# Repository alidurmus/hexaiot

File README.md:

# hexaiot
Open source hardware iot project

What is IOT?
The internet of things, or IoT, is a system of interrelated computing devices, mechanical and digital machines, objects, animals or people that are provided with unique identifiers (UIDs) and the ability to transfer data over a network without requiring human-to-human or human-to-computer interaction

Why is IOT?
Increasingly, organizations in a variety of industries are using IoT to operate more efficiently, better understand customers to deliver enhanced customer service, improve decision-making and increase the value of the business.

History Of IOT
Kevin Ashton, co-founder of the Auto-ID Center at MIT, first mentioned the internet of things in a presentation he made to Procter & Gamble (P&G) in 1999. Wanting to bring radio frequency ID (RFID) to the attention of P&G’s senior management, Ashton called his presentation “Internet of Things” to incorporate the cool new trend of 1999: the internet. MIT professor Neil Gershenfeld’s book, When Things Start to Think, also appearing in 1999, didn’t use the exact term but provided a clear vision of where IoT was headed.

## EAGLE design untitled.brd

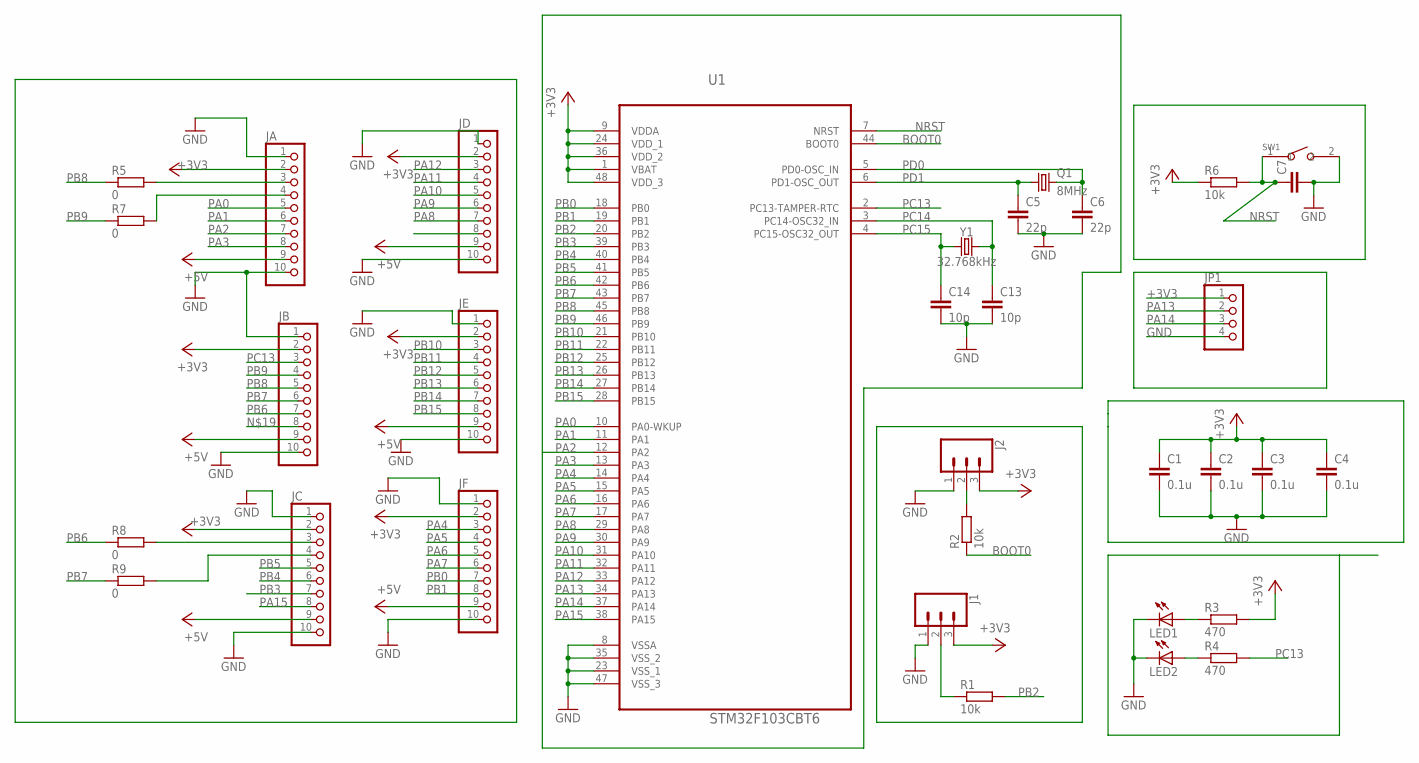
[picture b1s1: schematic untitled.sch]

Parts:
C1, C2, C3, C4: 0.1u; C0805K
C5, C6: 22p; C0805K
C7: C-EUC0805K; C0805K
C13, C14: 10p; C1206K
J1, J2: CONN_03; 1X03
JA: PINHD-1X10; 1X10-BIG
JB: PINHD-1X10; 1X10-BIG
JC: PINHD-1X10; 1X10-BIG
JD: PINHD-1X10; 1X10-BIG
JE: PINHD-1X10; 1X10-BIG
JF: PINHD-1X10; 1X10-BIG
JP1: PINHD-1X4; 1X04
LED1, LED2: LEDCHIPLED_0805; CHIPLED_0805
Q1: 8MHz; HC49/S
R1, R2, R6: 10k; R0805
R3, R4: 470; R0805
R5, R7, R8, R9: 0; R0805
SW1: SMD-BUTTON(2P-6.0X3.0X2.5MM)-DHT-1163S; SW2-4.0-6.0X3.0X2.5MM
U1: STM32F103CBT6; QFP50P900X900X160-48N
Y1: 32.768kHz; CRYSTAL-SMD-2X6-CYL

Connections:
+3V3: C1.1, C2.1, C3.1, C4.1, J1.3, J2.3, JA.2, JB.2, JC.2, JD.2, JE.2, JF.2, JP1.1, R3.2, R6.1, U1.1 (VBAT), U1.9 (VDDA), U1.24 (VDD_1), U1.36 (VDD_2), U1.48 (VDD_3)
+5V: JA.9, JB.9, JC.9, JD.9, JE.9, JF.9
BOOT0: R2.1, U1.44 (BOOT0)
GND: C1.2, C2.2, C3.2, C4.2, C5.2, C6.2, C7.2, C13.2, C14.2, J1.1, J2.1, JA.1, JA.10, JB.1, JB.10, JC.1, JC.10, JD.1, JD.10, JE.1, JE.10, JF.1, JF.10, JP1.4, LED1.C, LED2.C, SW1.2, U1.8 (VSSA), U1.23 (VSS_1), U1.35 (VSS_2), U1.47 (VSS_3)
unnamed: J1.2, R1.1
unnamed: J2.2, R2.2
unnamed: JA.3, R5.2
unnamed: LED1.A, R3.1
unnamed: JA.4, R7.2
unnamed: LED2.A, R4.1
unnamed: JC.3, R8.2
unnamed: JC.4, R9.2
NRST: C7.1, R6.2, SW1.1, U1.7 (NRST)
PA0: JA.5, U1.10 (PA0-WKUP)
PA1: JA.6, U1.11 (PA1)
PA2: JA.7, U1.12 (PA2)
PA3: JA.8, U1.13 (PA3)
PA4: JF.3, U1.14 (PA4)
PA5: JF.4, U1.15 (PA5)
PA6: JF.5, U1.16 (PA6)
PA7: JF.6, U1.17 (PA7)
PA8: JD.7, U1.29 (PA8)
PA9: JD.6, U1.30 (PA9)
PA10: JD.5, U1.31 (PA10)
PA11: JD.4, U1.32 (PA11)
PA12: JD.3, U1.33 (PA12)
PA13: JP1.2, U1.34 (PA13)
PA14: JP1.3, U1.37 (PA14)
PA15: JC.8, U1.38 (PA15)
PB0: JF.7, U1.18 (PB0)
PB1: JF.8, U1.19 (PB1)
PB2: R1.2, U1.20 (PB2)
PB3: JC.7, U1.39 (PB3)
PB4: JC.6, U1.40 (PB4)
PB5: JC.5, U1.41 (PB5)
PB6: JB.7, R8.1, U1.42 (PB6)
PB7: JB.6, R9.1, U1.43 (PB7)
PB8: JB.5, R5.1, U1.45 (PB8)
PB9: JB.4, R7.1, U1.46 (PB9)
PB10: JE.3, U1.21 (PB10)
PB11: JE.4, U1.22 (PB11)
PB12: JE.5, U1.25 (PB12)
PB13: JE.6, U1.26 (PB13)
PB14: JE.7, U1.27 (PB14)
PB15: JE.8, U1.28 (PB15)
PC13: JB.3, R4.2, U1.2 (PC13-TAMPER-RTC)
PC14: C13.1, U1.3 (PC14-OSC32_IN), Y1.X2 (2)
PC15: C14.1, U1.4 (PC15-OSC32_OUT), Y1.X1 (1)
PD0: C6.1, Q1.2, U1.5 (PD0-OSC_IN)
PD1: C5.1, Q1.1, U1.6 (PD1-OSC_OUT)

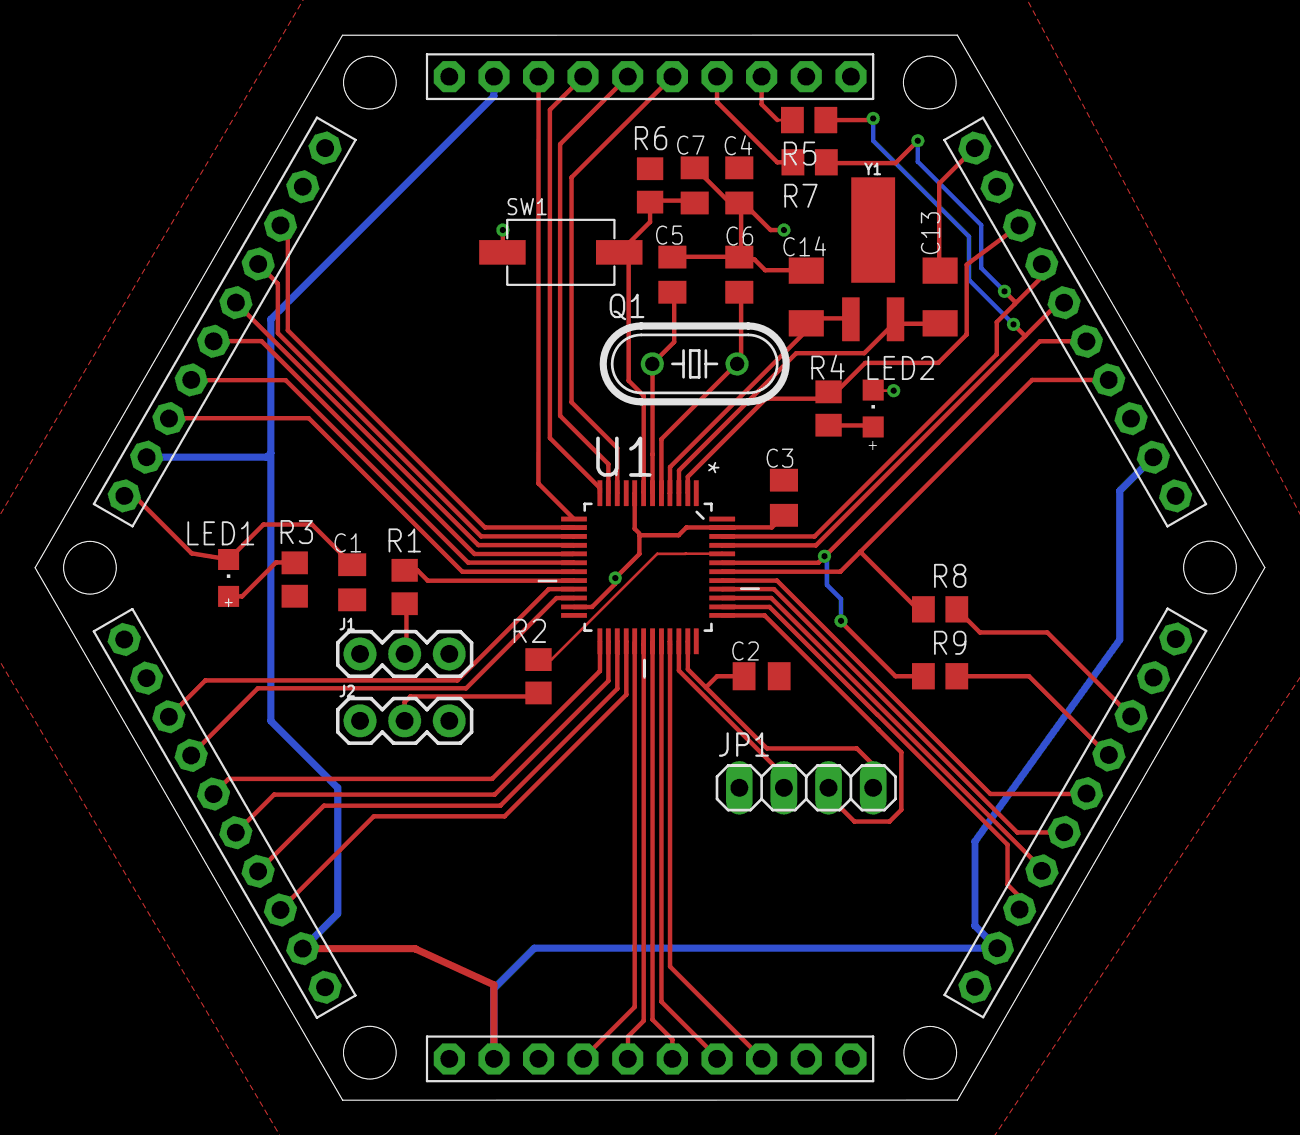
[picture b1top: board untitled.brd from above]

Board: 2 copper layers, 70.0 x 60.6 mm, 33 parts (0 on the bottom side), 50 nets.

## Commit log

2019-07-27 eagle project file
    added eagle project file
2019-07-27 dxf file
    dxf file

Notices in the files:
parts and their libraries:
SparkFun-Connectors: Licensing: Creative Commons ShareAlike 4.0 International - https://creativecommons.org/licenses/by-sa/4.0
